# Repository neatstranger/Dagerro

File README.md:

# Dagerro
>The first known attempt at astronomical photography was by Louis Jacques Mandé Daguerre, inventor of the daguerreotype process which bears his name, who attempted in 1839 to photograph the Moon. Tracking errors in guiding the telescope during the long exposure meant the photograph came out as an indistinct fuzzy spot. [Source](https://en.wikipedia.org/wiki/Astrophotography#:~:text=The%20first%20known%20attempt%20at,as%20an%20indistinct%20fuzzy%20spot.)

# Guide Timing
Some notes for myself as well as anyone reading. 
We need to move the steppers about 8 times per second and the Real Time Clock(RTC) doesn't allow for time resolution greater than 1 second. 
The RTC(DS3231) outputs 32,768 pulses per second on the 32K pin. We attach an interrupt to that pin with the following line.

`attachInterrupt(digitalPinToInterrupt(interruptPin), countCycles, CHANGE);`

Note the use of the `CHANGE` for activation. This means that we will capture one interrupt for each rise, and one for each fall.
With our second now divided up into 65,536 segments.

```
1 Degree = 60 ArcMinutes
1 ArcMinute = 60 ArcSeconds
1 Degree = 3600 ArcSeconds
```

How fast does the earth rotate? My previous assumption of ~1ArcSecond/Second~ is wrong. Let's do the math.
```
360° = 24 Hours
15° = 1 Hour or 60 Minutes or 3600 Seconds
1° or 3600 ArcSeconds = 4 Minutes or 240 Seconds
Math = 3600(ArcSeconds-Angle)/240 (Seconds-Time)
15 ArcSeconds(Angle) = 1 Second(Time)

```

The arduino receive exactly 1,658,880 pulses every 25.3125 seconds.
During this period of time, we need to take exactly 1500 steps.

python function to solve the problem.

```
x = 1
maxcount = 1500
xmult = 1105
ymult = 1107

while x <= maxcount:
    y = maxcount - x
    if (xmult*x)+(ymult*y) == 1658880:
        print(x)
        print(y)
        print((xmult*x) + (ymult*y))
    x+=1
```
I used this script, changing the values for xmult and ymult, until I got a result that looks like this:

```
810
690
1658880

```
Which means that if we take a step every 1105 interrupts, 810 times.
Followed by taking a step every 1107 interrupts, 690 times. 
We will have taken 1500 steps in exactly 25.3125 seconds. 

```
1500 Steps * 0.253125 ArcSeconds Per Step = 379.6875 ArcSeconds
379.6875 ArcSeconds / 25.3125 Seconds
15 ArcSeconds / Second
```

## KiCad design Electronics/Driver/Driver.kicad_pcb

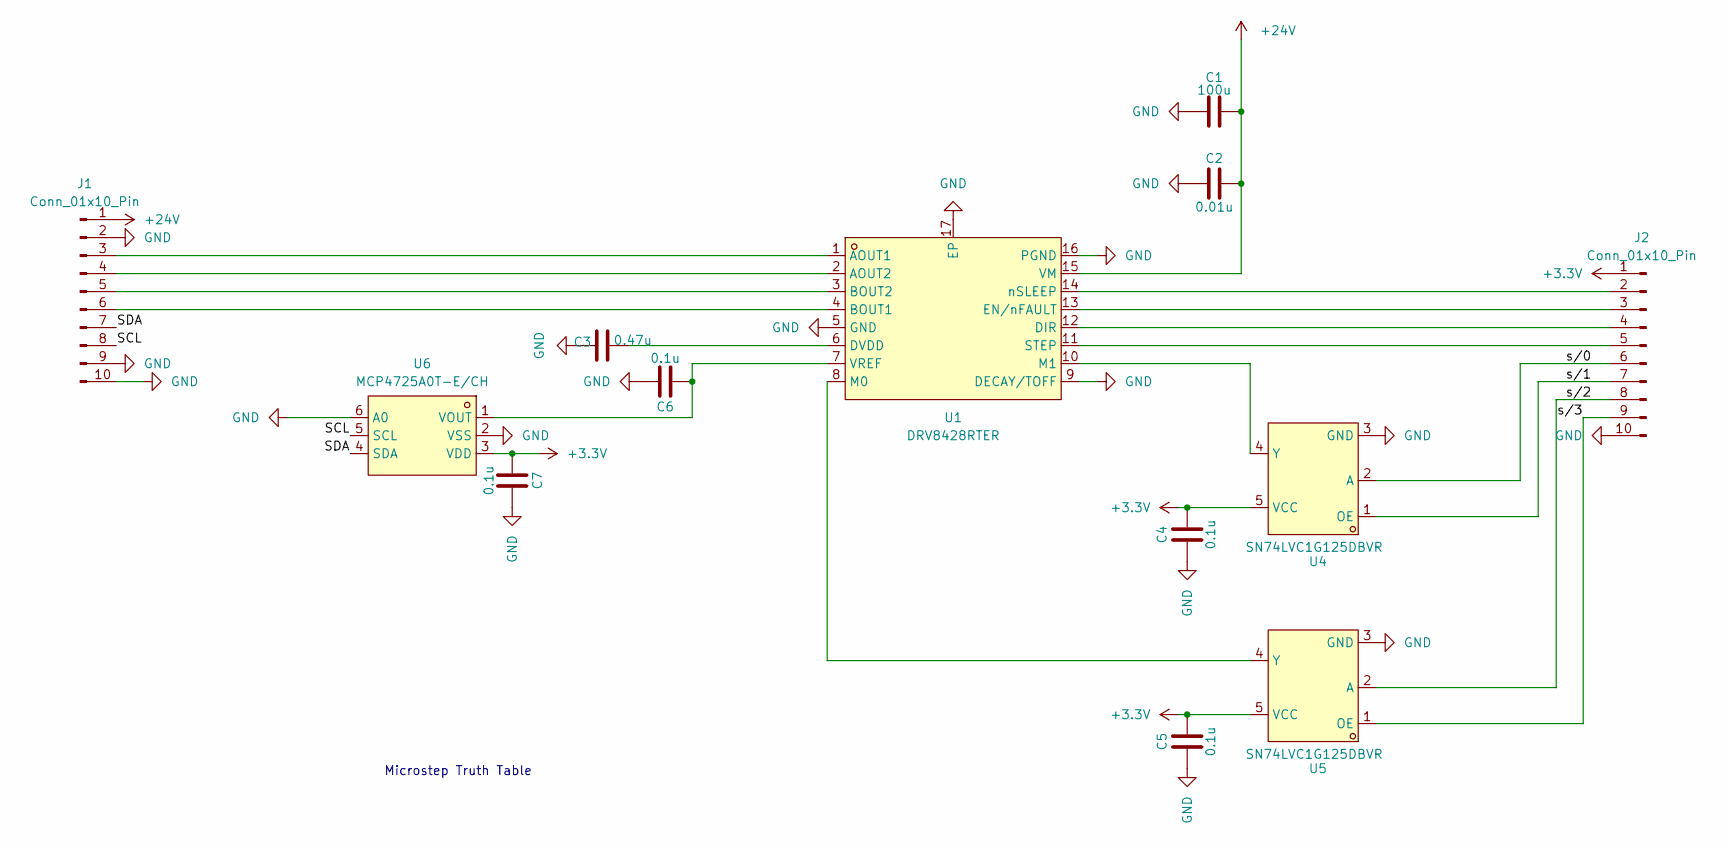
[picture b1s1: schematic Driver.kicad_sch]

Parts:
C1: 100u; C_1206_3216Metric_Pad1.33x1.80mm_HandSolder
C2: 0.01u; C_1206_3216Metric_Pad1.33x1.80mm_HandSolder
C3: 0.47u; C_1206_3216Metric_Pad1.33x1.80mm_HandSolder
C4, C5, C6, C7: 0.1u; C_1206_3216Metric_Pad1.33x1.80mm_HandSolder
J1, J2: Conn_01x10_Pin; PinSocket_1x10_P2.54mm_Vertical
U1: DRV8428RTER; WQFN-16_L3.0-W3.0-P0.50-BL-EP1.7; LCSC Part C2857955
U4, U5: SN74LVC1G125DBVR; SOT-23-5_L3.0-W1.7-P0.95-LS2.8-BL; LCSC Part C23654
U6: MCP4725A0T-E/CH; SOT-23-6_L2.9-W1.6-P0.95-LS2.8-BL; LCSC Part C144198

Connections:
+3.3V: C4.2, C5.2, C7.2, J2.1, U4.5 (VCC), U5.5 (VCC), U6.3 (VDD)
+24V: C1.2, C2.2, J1.1, U1.15 (VM)
/SCL: J1.8, U6.5 (SCL)
/SDA: J1.7, U6.4 (SDA)
GND: C1.1, C2.1, C3.1, C4.1, C5.1, C6.1, C7.1, J1.2, J1.9, J1.10, J2.10, U1.5 (GND), U1.9 (DECAY/TOFF), U1.16 (PGND), U1.17 (EP), U4.3 (GND), U5.3 (GND), U6.2 (VSS), U6.6 (A0)
unnamed: J1.3, U1.1 (AOUT1)
unnamed: J1.4, U1.2 (AOUT2)
unnamed: J1.5, U1.3 (BOUT2)
unnamed: J1.6, U1.4 (BOUT1)
unnamed: J2.2, U1.14 (nSLEEP)
unnamed: J2.3, U1.13 (EN/nFAULT)
unnamed: J2.4, U1.12 (DIR)
unnamed: J2.5, U1.11 (STEP)
unnamed: J2.6, U4.2 (A)
unnamed: J2.7, U4.1 (OE)
unnamed: J2.8, U5.2 (A)
unnamed: J2.9, U5.1 (OE)
unnamed: C3.2, U1.6 (DVDD)
unnamed: U1.8 (M0), U5.4 (Y)
unnamed: U1.10 (M1), U4.4 (Y)
unnamed: C6.2, U1.7 (VREF), U6.1 (VOUT)

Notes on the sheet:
Microstep Truth Table

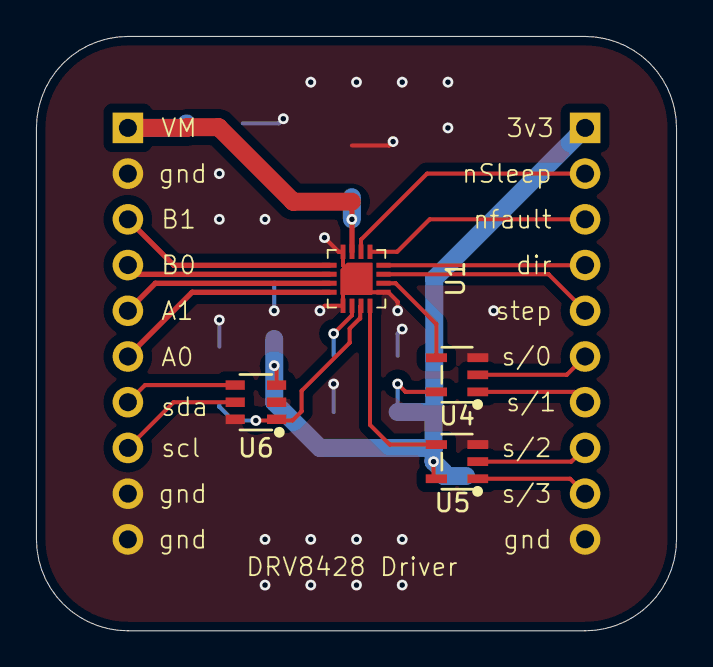
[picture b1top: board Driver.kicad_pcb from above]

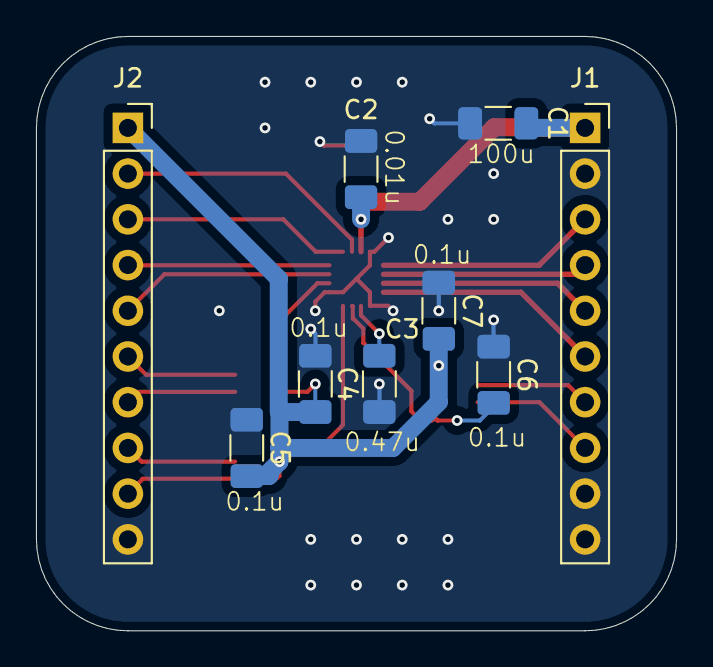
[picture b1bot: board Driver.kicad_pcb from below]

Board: 2 copper layers, 35.6 x 33.0 mm, 13 parts (9 on the bottom side), 21 nets.

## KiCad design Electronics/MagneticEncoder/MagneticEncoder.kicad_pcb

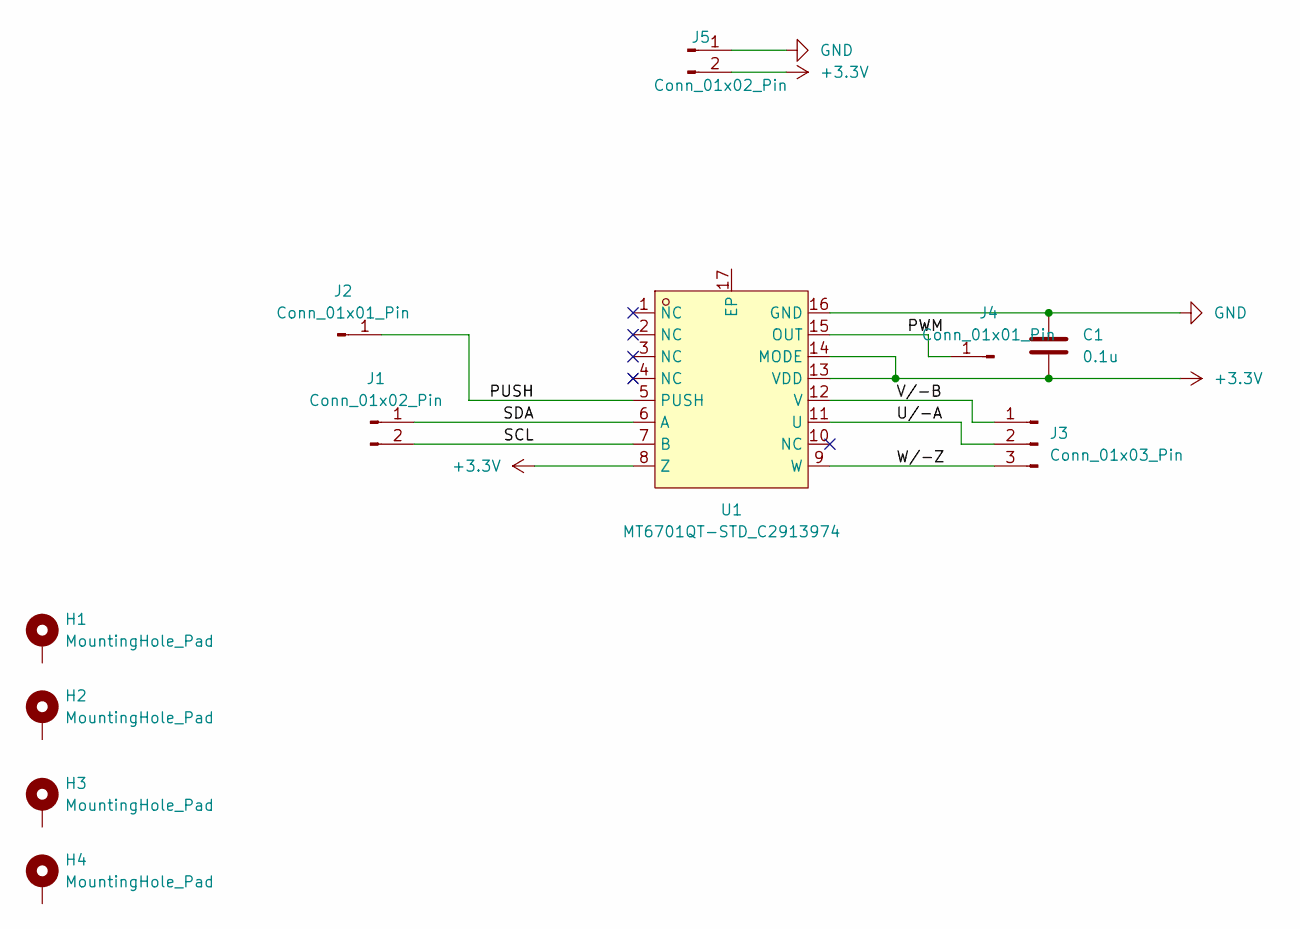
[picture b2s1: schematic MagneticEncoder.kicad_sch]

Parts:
C1: 0.1u; C_1206_3216Metric_Pad1.33x1.80mm_HandSolder
H1, H2, H3, H4: MountingHole_Pad; MountingHole_3.2mm_M3_DIN965_Pad_TopBottom
J1, J5: Conn_01x02_Pin; PinHeader_1x02_P2.54mm_Vertical
J2, J4: Conn_01x01_Pin; PinHeader_1x01_P2.54mm_Vertical
J3: Conn_01x03_Pin; PinHeader_1x03_P2.54mm_Vertical
U1: MT6701QT-STD_C2913974; QFN-16_L3.0-W3.0-P0.50-TL-EP1.7; LCSC Part C2913974

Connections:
+3.3V: C1.2, J5.2, U1.8 (Z), U1.13 (VDD), U1.14 (MODE)
/PUSH: J2.1, U1.5 (PUSH)
/PWM: J4.1, U1.15 (OUT)
/SCL: J1.2, U1.7 (B)
/SDA: J1.1, U1.6 (A)
/U/-A: J3.2, U1.11 (U)
/V/-B: J3.1, U1.12 (V)
/W/-Z: J3.3, U1.9 (W)
GND: C1.1, J5.1, U1.16 (GND)

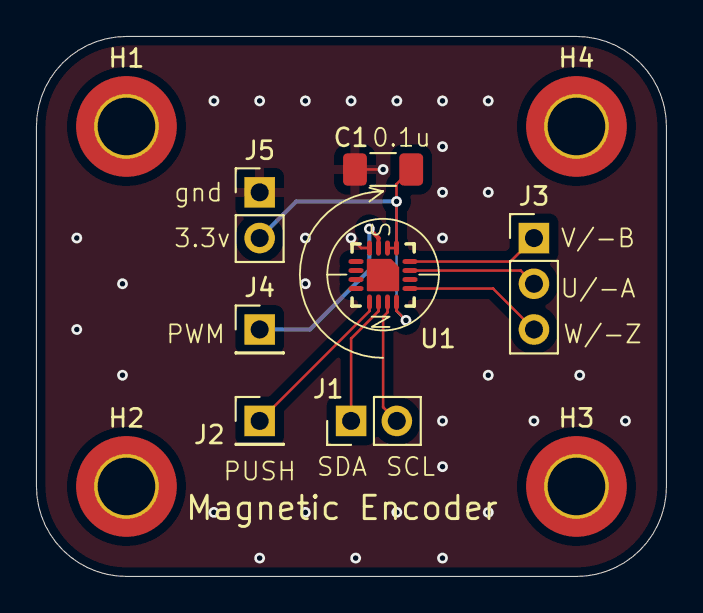
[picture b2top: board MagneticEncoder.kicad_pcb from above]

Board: 2 copper layers, 35.0 x 30.0 mm, 11 parts (0 on the bottom side), 9 nets.

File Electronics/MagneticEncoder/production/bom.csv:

Designator,Footprint,Quantity,Value,LCSC Part #
C1,1206,1,0.1u,
"J1, J5",PinHeader_1x02_P2.54mm_Vertical,2,Conn_01x02_Pin,
"J2, J4",PinHeader_1x01_P2.54mm_Vertical,2,Conn_01x01_Pin,
J3,PinHeader_1x03_P2.54mm_Vertical,1,Conn_01x03_Pin,
U1,QFN-16_L3.0-W3.0-P0.50-TL-EP1.7,1,MT6701QT-STD_C2913974,C2913974

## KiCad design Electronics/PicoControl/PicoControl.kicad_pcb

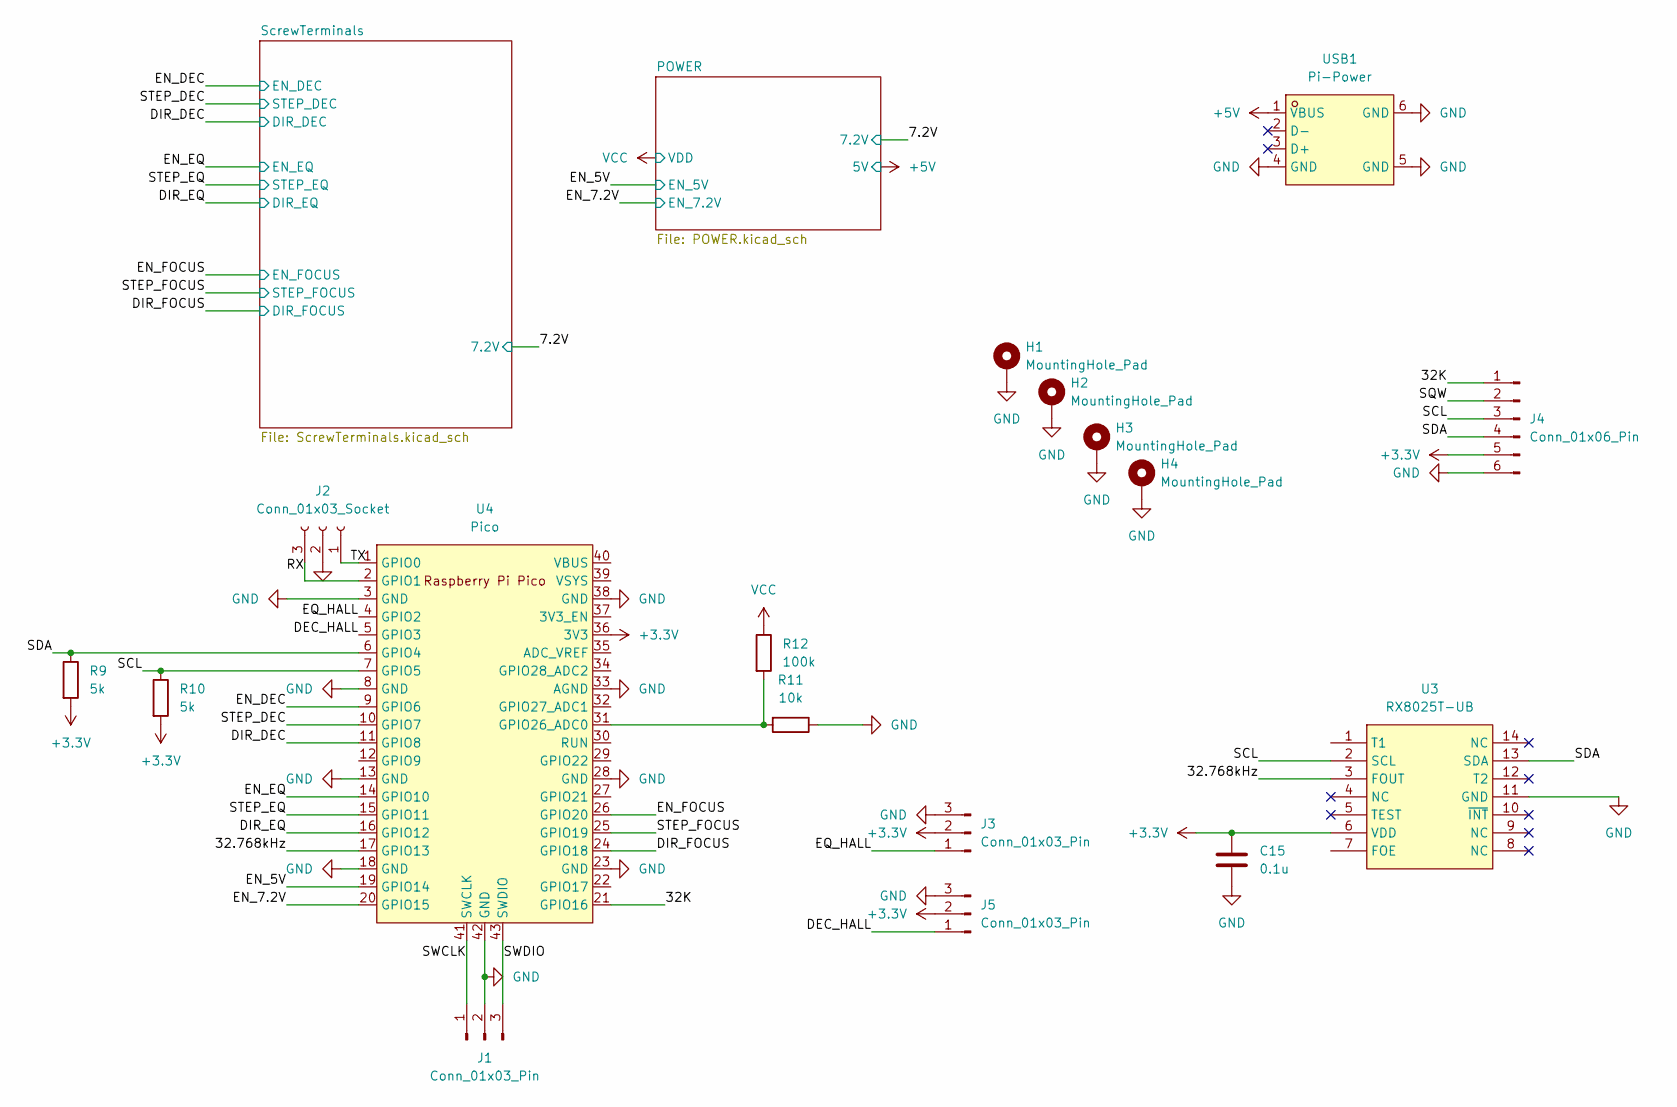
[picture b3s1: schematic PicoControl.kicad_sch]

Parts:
C15: 0.1u; C_1206_3216Metric_Pad1.33x1.80mm_HandSolder
H1, H2, H3, H4: MountingHole_Pad; MountingHole_5.3mm_M5_DIN965_Pad
J1: Conn_01x03_Pin; PinHeader_1x03_P2.54mm_Vertical
J2: Conn_01x03_Socket; PinHeader_1x03_P2.54mm_Vertical
J3, J5: Conn_01x03_Pin; PinHeader_1x03_P2.54mm_Horizontal
J4: Conn_01x06_Pin; PinHeader_1x06_P2.54mm_Vertical
R9, R10: 5k; R_1206_3216Metric_Pad1.30x1.75mm_HandSolder
R11: 10k; R_1206_3216Metric_Pad1.30x1.75mm_HandSolder
R12: 100k; R_1206_3216Metric_Pad1.30x1.75mm_HandSolder
U3: RX8025T-UB; SOIC-14_L10.1-W5.0-P1.27-LS7.4-BL; LCSC Part C17353
U4: Pico; RPi_Pico_SMD_TH
USB1: Pi-Power; USB-A-TH_USB-231-ARY; LCSC Part C720525

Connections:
+3.3V: C15.2, J3.2, J4.5, J5.2, R9.2, R10.2, U3.6 (VDD), U4.36 (3V3)
+5V: USB1.1 (VBUS); also elsewhere on the board
/32.768kHz: U3.3 (FOUT), U4.17 (GPIO13)
/32K: J4.1, U4.21 (GPIO16)
/DEC_HALL: J5.1, U4.5 (GPIO3)
/DIR_DEC: U4.11 (GPIO8); also elsewhere on the board
/DIR_EQ: U4.16 (GPIO12); also elsewhere on the board
/DIR_FOCUS: U4.24 (GPIO18); also elsewhere on the board
/EN_5V: U4.19 (GPIO14); also elsewhere on the board
/EN_7.2V: U4.20 (GPIO15); also elsewhere on the board
/EN_DEC: U4.9 (GPIO6); also elsewhere on the board
/EN_EQ: U4.14 (GPIO10); also elsewhere on the board
/EN_FOCUS: U4.26 (GPIO20); also elsewhere on the board
/EQ_HALL: J3.1, U4.4 (GPIO2)
/RX: J2.3, U4.2 (GPIO1)
/SCL: J4.3, R10.1, U3.2 (SCL), U4.7 (GPIO5)
/SDA: J4.4, R9.1, U3.13 (SDA), U4.6 (GPIO4)
/SQW: J4.2
/STEP_DEC: U4.10 (GPIO7); also elsewhere on the board
/STEP_EQ: U4.15 (GPIO11); also elsewhere on the board
/STEP_FOCUS: U4.25 (GPIO19); also elsewhere on the board
/SWCLK: J1.1, U4.41 (SWCLK)
/SWDIO: J1.3, U4.43 (SWDIO)
/TX: J2.1, U4.1 (GPIO0)
GND: C15.1, H1.1, H2.1, H3.1, H4.1, J1.2, J2.2, J3.3, J4.6, J5.3, R11.1, U3.11 (GND), U4.3 (GND), U4.8 (GND), U4.13 (GND), U4.18 (GND), U4.23 (GND), U4.28 (GND), U4.33 (AGND), U4.38 (GND), U4.42 (GND), USB1.4 (GND), USB1.5 (GND), USB1.6 (GND); also elsewhere on the board
unnamed: R11.2, R12.2, U4.31 (GPIO26_ADC0)
VCC: R12.1; also elsewhere on the board

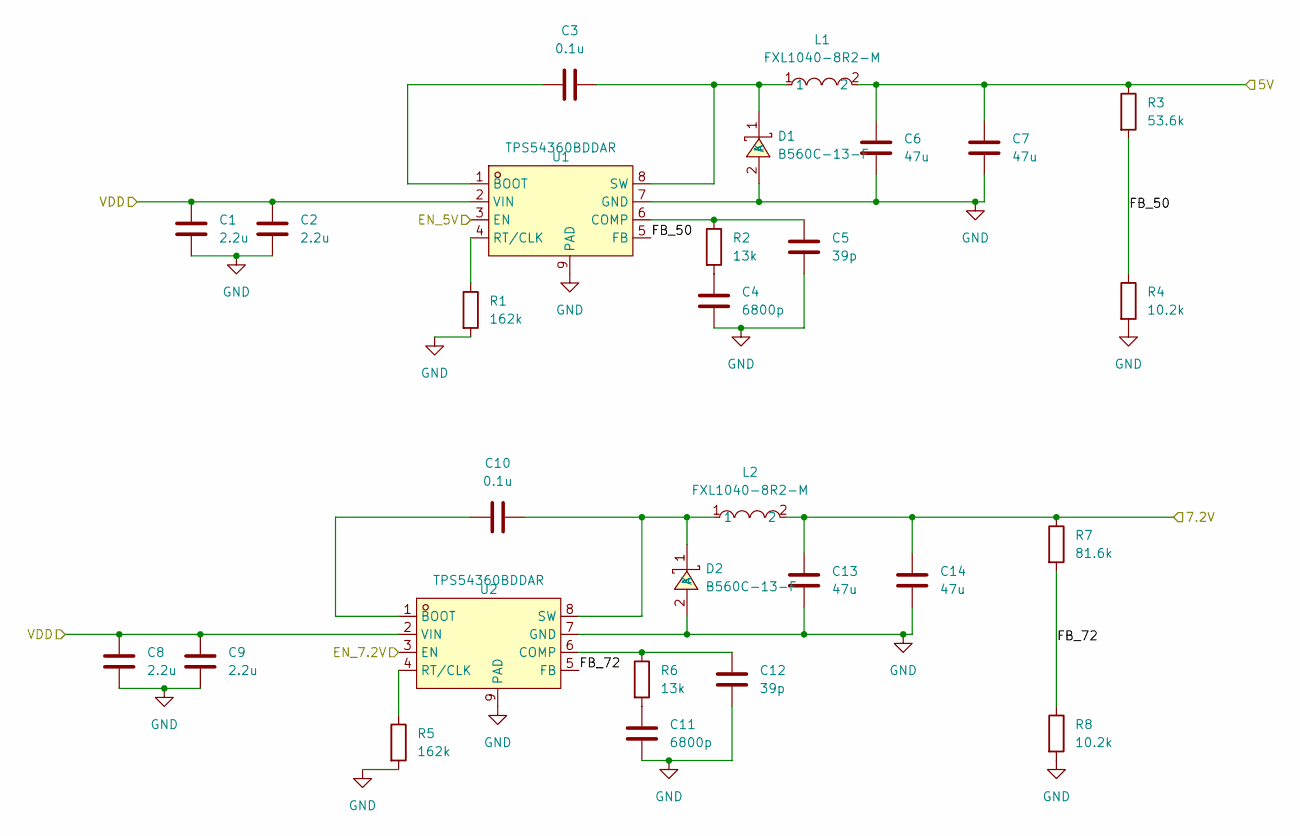
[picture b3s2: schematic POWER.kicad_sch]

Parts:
C1, C2, C8, C9: 2.2u; C_1206_3216Metric; LCSC Part C170101
C3, C10: 0.1u; C_1206_3216Metric_Pad1.33x1.80mm_HandSolder; LCSC Part C56392
C4, C11: 6800p; C_1206_3216Metric_Pad1.33x1.80mm_HandSolder; LCSC Part C2760541
C5, C12: 39p; C_1206_3216Metric_Pad1.33x1.80mm_HandSolder; LCSC Part C5186878
C6, C7, C13, C14: 47u; C_1206_3216Metric; LCSC Part C94034
D1, D2: B560C-13-F; SMC_L7.1-W6.2-LS8.1-RD; LCSC Part C85100
L1, L2: FXL1040-8R2-M; IND-SMD_L11.5-W10.0_FXL1040; LCSC Part C167232
R1, R5: 162k; R_1206_3216Metric_Pad1.30x1.75mm_HandSolder; LCSC Part C22815
R2, R6: 13k; R_1206_3216Metric_Pad1.30x1.75mm_HandSolder; LCSC Part C445658
R3: 53.6k; R_1206_3216Metric_Pad1.30x1.75mm_HandSolder; LCSC Part C21398
R4, R8: 10.2k; R_1206_3216Metric_Pad1.30x1.75mm_HandSolder; LCSC Part C217771
R7: 81.6k; R_1206_3216Metric_Pad1.30x1.75mm_HandSolder; LCSC Part C21398
U1, U2: TPS54360BDDAR; SOIC-8_L5.0-W4.0-P1.27-LS6.0-BL-EP2.0; LCSC Part C524806

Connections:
+5V: C6.1, C7.1, L1.2, R3.1; also elsewhere on the board
/7.2V: C13.1, C14.1, L2.2, R7.1; also elsewhere on the board
/EN_5V: U1.3 (EN); also elsewhere on the board
/EN_7.2V: U2.3 (EN); also elsewhere on the board
/POWER/FB_50: R3.2, R4.1, U1.5 (FB)
/POWER/FB_72: R7.2, R8.1, U2.5 (FB)
GND: C1.2, C2.2, C4.2, C5.2, C6.2, C7.2, C8.2, C9.2, C11.2, C12.2, C13.2, C14.2, D1.2 (A), D2.2 (A), R1.2, R4.2, R5.2, R8.2, U1.7 (GND), U1.9 (PAD), U2.7 (GND), U2.9 (PAD); also elsewhere on the board
unnamed: C4.1, R2.2
unnamed: C11.1, R6.2
unnamed: C3.2, D1.1 (K), L1.1, U1.8 (SW)
unnamed: C10.2, D2.1 (K), L2.1, U2.8 (SW)
unnamed: C3.1, U1.1 (BOOT)
unnamed: C5.1, R2.1, U1.6 (COMP)
unnamed: R1.1, U1.4 (RT/CLK)
unnamed: C10.1, U2.1 (BOOT)
unnamed: C12.1, R6.1, U2.6 (COMP)
unnamed: R5.1, U2.4 (RT/CLK)
VCC: C1.1, C2.1, C8.1, C9.1, U1.2 (VIN), U2.2 (VIN); also elsewhere on the board

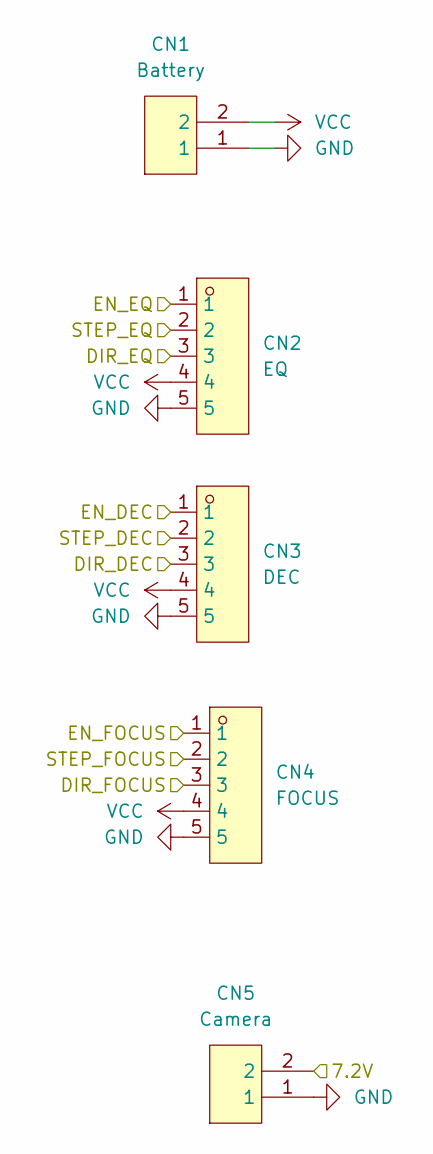
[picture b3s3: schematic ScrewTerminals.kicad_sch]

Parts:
CN1: Battery; CONN-TH_2P-P5.00_WJ500V-5.08-2P; LCSC Part C8465
CN2: EQ; CONN-TH_5P-P5.08_DIBO_DB128V-5.08-5P-GN-S; LCSC Part C2927513
CN3: DEC; CONN-TH_5P-P5.08_DIBO_DB128V-5.08-5P-GN-S; LCSC Part C2927513
CN4: FOCUS; CONN-TH_5P-P5.08_DIBO_DB128V-5.08-5P-GN-S; LCSC Part C2927513
CN5: Camera; CONN-TH_2P-P5.00_WJ500V-5.08-2P; LCSC Part C8465

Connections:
/7.2V: CN5.2; also elsewhere on the board
/DIR_DEC: CN3.3; also elsewhere on the board
/DIR_EQ: CN2.3; also elsewhere on the board
/DIR_FOCUS: CN4.3; also elsewhere on the board
/EN_DEC: CN3.1; also elsewhere on the board
/EN_EQ: CN2.1; also elsewhere on the board
/EN_FOCUS: CN4.1; also elsewhere on the board
/STEP_DEC: CN3.2; also elsewhere on the board
/STEP_EQ: CN2.2; also elsewhere on the board
/STEP_FOCUS: CN4.2; also elsewhere on the board
GND: CN1.1, CN2.5, CN3.5, CN4.5, CN5.1; also elsewhere on the board
VCC: CN1.2, CN2.4, CN3.4, CN4.4; also elsewhere on the board

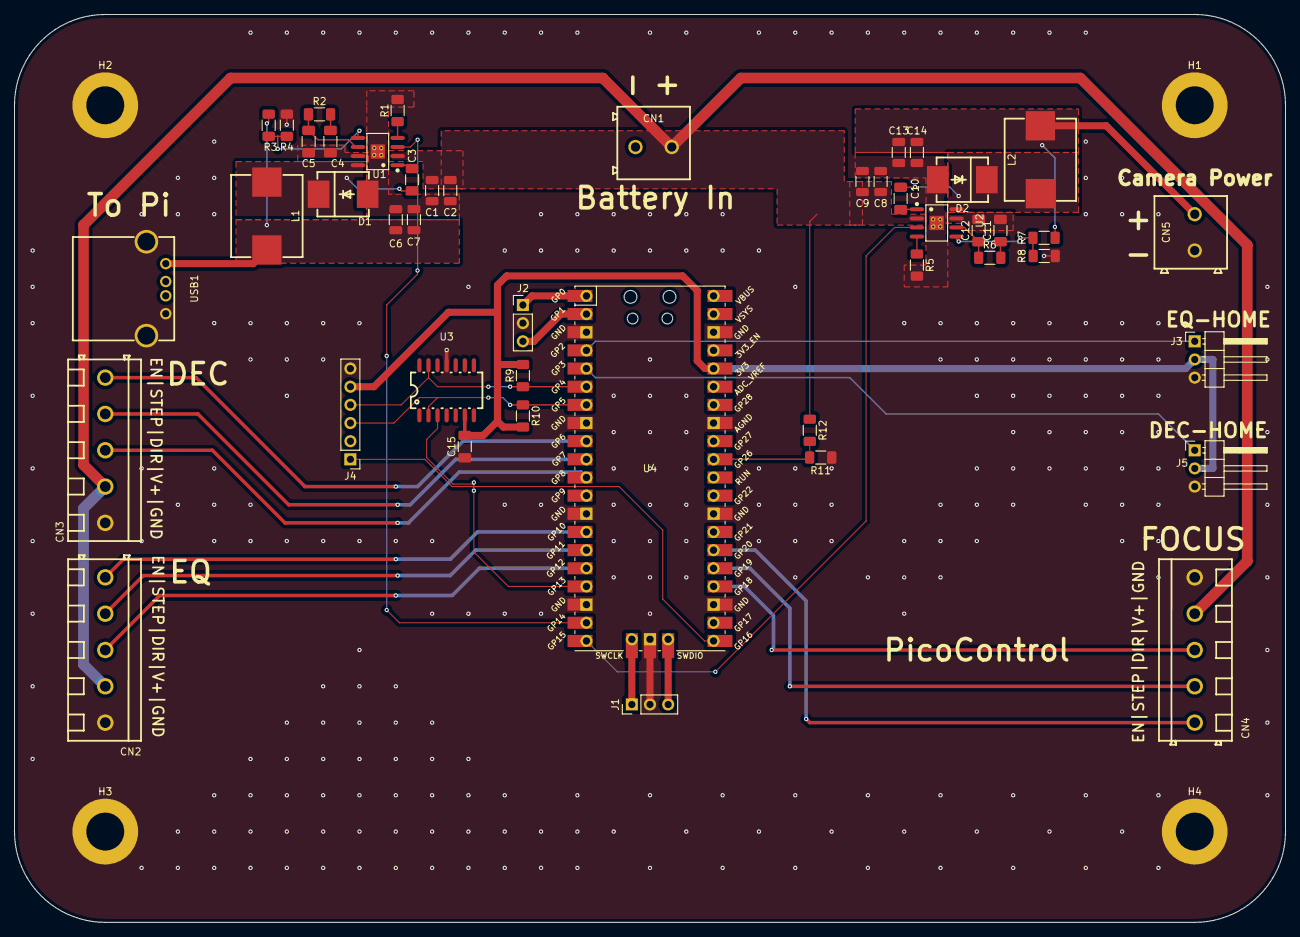
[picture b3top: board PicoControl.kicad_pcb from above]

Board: 2 copper layers, 177.8 x 127.0 mm, 50 parts (0 on the bottom side), 39 nets.

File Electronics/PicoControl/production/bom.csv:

Designator,Footprint,Quantity,Value,LCSC Part #
"C1, C2, C8, C9",1206,4,2.2u,C170101
"C10, C3",1206,2,0.1u,C56392
"C11, C4",1206,2,6800p,C2760541
"C12, C5",1206,2,39p,C5186878
"C13, C14, C6, C7",1206,4,47u,C94034
C15,1206,1,0.1u,
CN1,CONN-TH_2P-P5.00_WJ500V-5.08-2P,1,Battery,C8465
CN2,CONN-TH_5P-P5.08_DIBO_DB128V-5.08-5P-GN-S,1,EQ,C2927513
CN3,CONN-TH_5P-P5.08_DIBO_DB128V-5.08-5P-GN-S,1,DEC,C2927513
CN4,CONN-TH_5P-P5.08_DIBO_DB128V-5.08-5P-GN-S,1,FOCUS,C2927513
CN5,CONN-TH_2P-P5.00_WJ500V-5.08-2P,1,Camera,C8465
"D1, D2",SMC_L7.1-W6.2-LS8.1-RD,2,B560C-13-F,C85100
J1,PinHeader_1x03_P2.54mm_Vertical,1,Conn_01x03_Pin,
J2,PinHeader_1x03_P2.54mm_Vertical,1,Conn_01x03_Socket,
J4,PinHeader_1x06_P2.54mm_Vertical,1,Conn_01x06_Pin,
"L1, L2",IND-SMD_L11.5-W10.0_FXL1040,2,FXL1040-8R2-M,C167232
"R1, R5",1206,2,162k,C22815
"R10, R9",1206,2,5k,
R11,1206,1,10k,
R12,1206,1,100k,
"R2, R6",1206,2,13k,C445658
R3,1206,1,53.6k,C21398
"R4, R8",1206,2,10.2k,C217771
R7,1206,1,81.6k,C21398
"U1, U2",SOIC-8_L5.0-W4.0-P1.27-LS6.0-BL-EP2.0,2,TPS54360BDDAR,C524806
U3,SOIC-14_L10.1-W5.0-P1.27-LS7.4-BL,1,RX8025T-UB,C17353
U4,RPi_Pico_SMD_TH,1,Pico,
USB1,USB-A-TH_USB-231-ARY,1,Pi-Power,C720525

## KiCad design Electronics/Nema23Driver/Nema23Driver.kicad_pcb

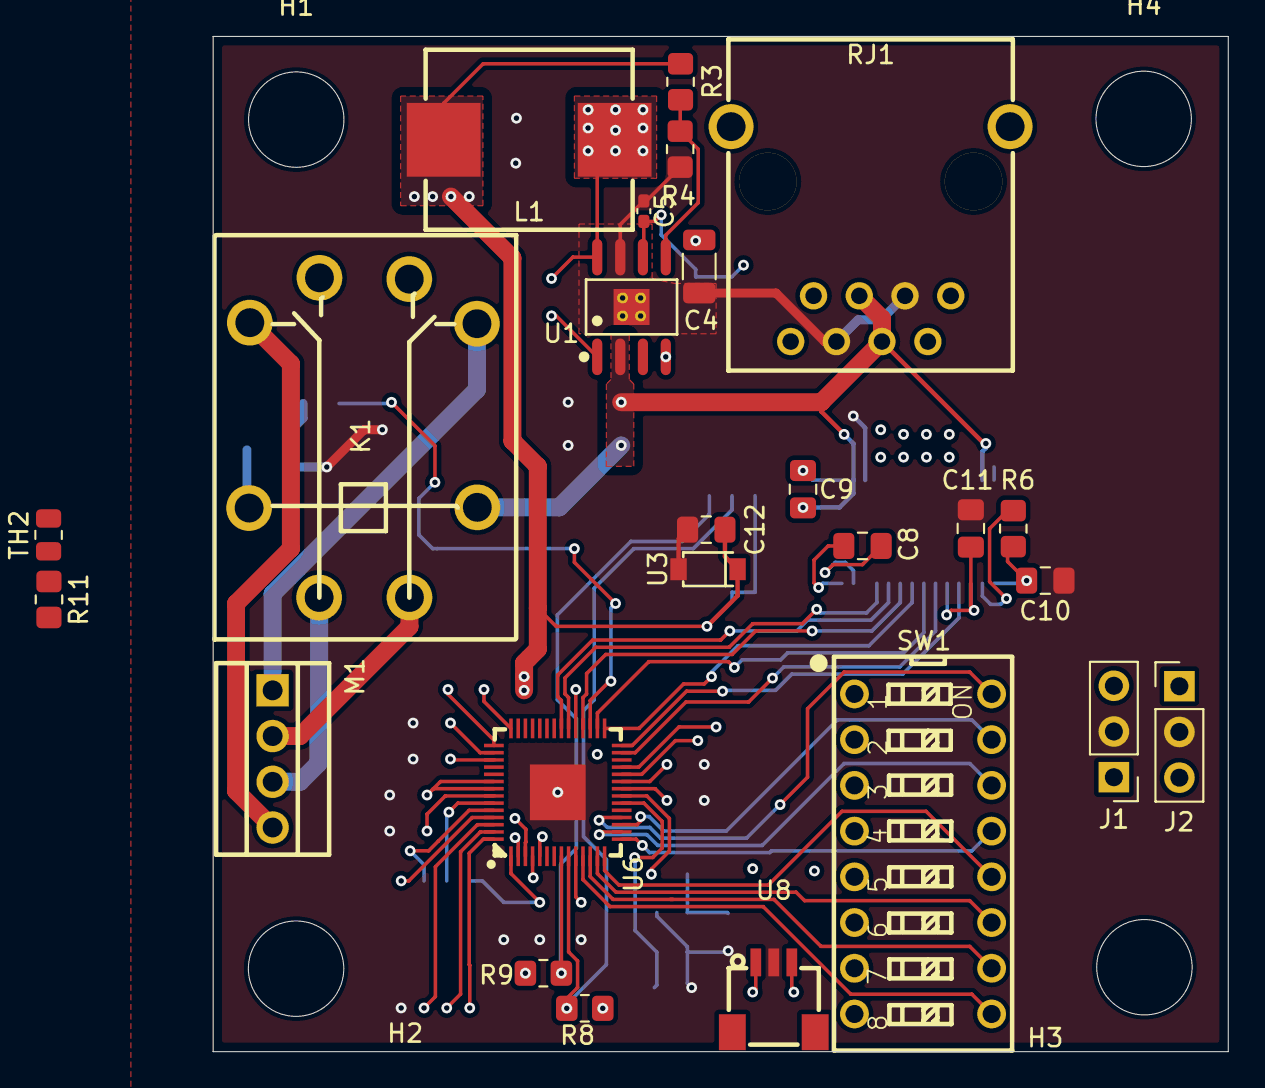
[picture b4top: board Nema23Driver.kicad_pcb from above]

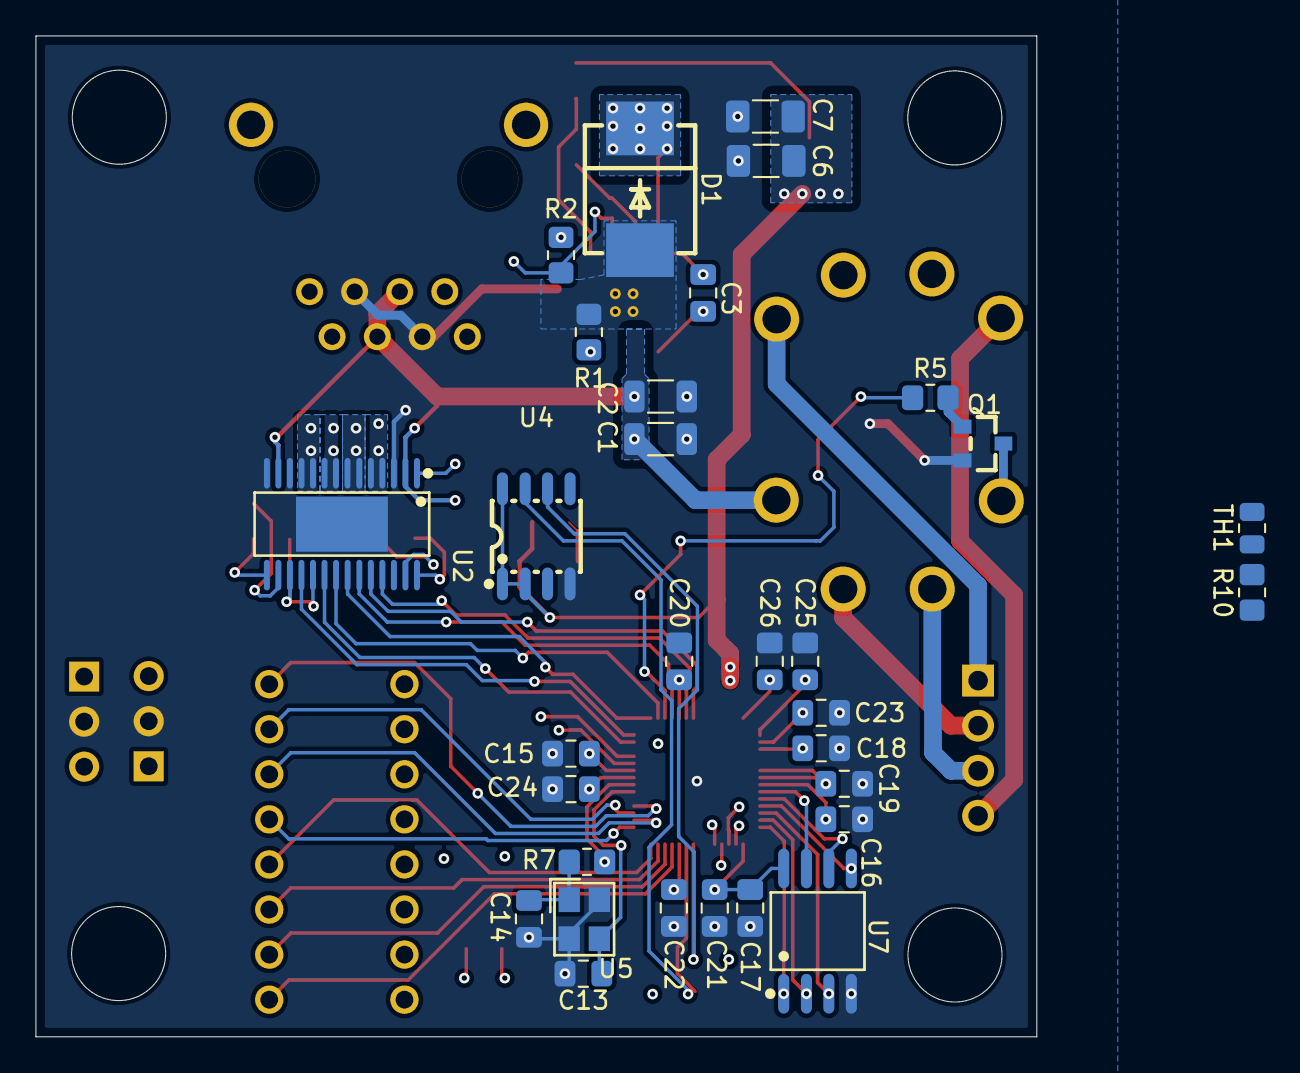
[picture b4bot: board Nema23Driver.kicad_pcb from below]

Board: 4 copper layers, 56.4 x 56.4 mm, 60 parts (31 on the bottom side), 58 nets.

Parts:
C1, C2: 2.2u; C_1206_3216Metric
C3, C11, C12, C15, C16, C17, C20, C21, C22, C23, C24, C25, C26: 0.1u; C_0805_2012Metric_Pad1.18x1.45mm_HandSolder
C4: 6800p; C_1206_3216Metric
C5: 39p; C_0402_1005Metric_Pad0.74x0.62mm_HandSolder
C6, C7: 47u; C_1206_3216Metric_Pad1.33x1.80mm_HandSolder
C8: 0.022u; C_0805_2012Metric_Pad1.18x1.45mm_HandSolder
C9: 0.22u; C_0805_2012Metric_Pad1.18x1.45mm_HandSolder
C10: 0.47u; C_0805_2012Metric_Pad1.18x1.45mm_HandSolder
C13, C14: 15p; C_0805_2012Metric_Pad1.18x1.45mm_HandSolder
C18, C19: 1u; C_0805_2012Metric_Pad1.18x1.45mm_HandSolder
D1: B560C-13-F; SMC_L7.1-W6.2-LS8.1-RD
H1, H2, H3, H4: MountingHole_Pad; MountingHole_5.3mm_M5
J1, J2: Conn_01x03_Socket; PinHeader_1x03_P2.54mm_Vertical
K1: SRE-24VDC-SL-2C; RELAY-TH_SRE-12VDC-SL-2C
L1: FXL1040-8R2-M; IND-SMD_L11.5-W10.0_FXL1040
M1: Stepper_Motor_bipolar; CONN-TH_DB125-2.54-4P-GN
Q1: AO3400_C2938367; SOT-23_L2.9-W1.3-P1.90-LS2.4-BR
R1: 162k; R_0805_2012Metric_Pad1.20x1.40mm_HandSolder
R2: 13k; R_0805_2012Metric_Pad1.20x1.40mm_HandSolder
R3: 31.6k; R_0805_2012Metric_Pad1.20x1.40mm_HandSolder
R4: 10.2k; R_0805_2012Metric_Pad1.20x1.40mm_HandSolder
R5, R7: 1k; R_0805_2012Metric_Pad1.20x1.40mm_HandSolder
R6: 10k; R_0805_2012Metric_Pad1.20x1.40mm_HandSolder
R8, R9, R10, R11: 5k; R_0805_2012Metric_Pad1.20x1.40mm_HandSolder
RJ1: R-RJ45R10P-B000; RJ45-TH_R-RJ45R10P-B000
SW1: DS-08BLP; SW-TH_16P-L21.9-W9.9-P2.54-LS7.6
TH1, TH2: 10K; R_0805_2012Metric
U1: TPS54360BDDAR; SOIC-8_L5.0-W4.0-P1.27-LS6.0-BL-EP2.0
U2: DRV8434SPWPR; HTSSOP-28_L9.7-W4.4-P0.65-LS6.4-BL-EP-5
U3: PTVS6V0S1UR_C18723426; SOD-123_L2.7-W1.6-LS3.7-RD
U4: MT6701CT-STD-R; SOP-8_L4.9-W3.9-P1.27-LS6.0-BL
U5: ABM8-272-T3_C20625731; CRYSTAL-SMD_4P-L3.2-W2.5-BL
U6: RP2040; LQFN-56_L7.0-W7.0-P0.4-EP
U7: W25Q128JVSIQTR; SOIC-8_L5.3-W5.3-P1.27-LS8.0-BL
U8: SM03B-SRSS-TB(LF)(SN)(P); CONN-SMD_SM03B-SRSS-TB-LF-SN-P

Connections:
+1V1: C15.2, C16.2, C18.2, U6.23 (DVDD), U6.45 (VREG_VOUT), U6.50 (DVDD)
+3.3V: C6.1, C7.1, C11.2, C12.2, C17.2, C19.2, C20.2, C21.2, C22.2, C23.2, C24.2, C25.2, C26.2, L1.2, R3.1, R8.2, R9.1, SW1.1 (PIN1), SW1.2 (PIN2), SW1.3 (PIN3), SW1.4 (PIN4), SW1.5 (PIN5), SW1.6 (PIN6), SW1.7 (PIN7), SW1.8 (PIN8), TH1.2, TH2.2, U2.17 (VREF), U2.19 (VSDO), U3.1 (K), U4.1 (VDD), U4.2 (MODE), U4.8 (Z), U6.1 (IOVDD), U6.10 (IOVDD), U6.22 (IOVDD), U6.33 (IOVDD), U6.42 (IOVDD), U6.43 (ADC_AVDD), U6.44 (VREG_IN), U6.48 (USB_VDD), U6.49 (IOVDD), U7.8 (VCC)
/DIR: U2.24 (DIR), U6.35 (GPIO23)
/EN: U2.25 (ENBLE), U6.34 (GPIO22)
/EN_MOT: R5.1, U6.31 (GPIO20)
/Magnetic Sensor/SCL: R8.1, U4.7 (B), U6.9 (GPIO7)
/Magnetic Sensor/SDA: R9.2, U4.6 (A), U6.8 (GPIO6)
/Motor/A0: K1.6, M1.2 (-)
/Motor/A0.Enabled: K1.8, U2.4 (AOUT1), U2.5 (AOUT1)
/Motor/A1: K1.7, M1.1, U2.6 (AOUT2), U2.7 (AOUT2)
/Motor/B0: K1.3, M1.3
/Motor/B0.Enabled: K1.5, U2.10 (BOUT1), U2.11 (BOUT1)
/Motor/B1: K1.4, M1.4, U2.8 (BOUT2), U2.9 (BOUT2)
/Motor/CS: U2.18 (NSCS), U6.28 (GPIO17)
/Motor/SCLK: U2.22 (SCLK), U6.29 (GPIO18)
/Motor/SDI: U2.21 (SDI), U6.30 (GPIO19)
/Motor/SDO: U2.20 (SDO), U6.27 (GPIO16)
/Power/Dir: RJ1.8, U6.4 (GPIO2)
/Power/FB: R3.2, R4.1, U1.5 (FB)
/Power/Step: RJ1.1, U6.5 (GPIO3)
/RP2040/ADC2: R11.1, TH2.1, U6.40 (GPIO28_ADC2)
/RP2040/ADC3: R10.1, TH1.1, U6.41 (GPIO29_ADC3)
/RP2040/CLK: U6.52 (QSPI_SCLK), U7.6 (CLK)
/RP2040/D0: U6.53 (QSPI_SD0), U7.5 (DI)
/RP2040/D1: U6.55 (QSPI_SD1), U7.2 (DO)
/RP2040/D2: U6.54 (QSPI_SD2), U7.3 (IO2)
/RP2040/D3: U6.51 (QSPI_SD3), U7.7 (IO3)
/RP2040/SS: U6.56 (QSPI_SS), U7.1 (~CS)
/RP2040/UART0_RX: J1.3, U6.3 (GPIO1)
/RP2040/UART0_TX: J1.1, U6.2 (GPIO0)
/STEP: U2.23 (STEP), U6.32 (GPIO21)
/SWCLK: J2.3, U6.24 (SWCLK), U8.1
/SWDIO: J2.1, U6.25 (SWD), U8.3
GND: C1.2, C2.2, C4.2, C5.2, C6.2, C7.2, C10.1, C11.1, C12.1, C13.2, C14.1, C15.1, C16.1, C17.1, C18.1, C19.1, C20.1, C21.1, C22.1, C23.1, C24.1, C25.1, C26.1, D1.2 (A), J1.2, J2.2, Q1.2 (S), R1.2, R4.2, R10.2, R11.2, RJ1.3, RJ1.6, U1.7 (GND), U1.9 (PAD), U2.3 (PGND), U2.12 (PGND), U2.14 (GND), U2.29 (EP), U3.2 (A), U4.4 (GND), U5.2 (GND), U5.4 (GND), U6.57 (GND), U7.4 (GND), U8.2
unnamed: C4.1, R2.2
unnamed: C14.2, R7.1, U5.1
unnamed: C3.2, D1.1 (K), L1.1, U1.8 (SW)
unnamed: K1.1, Q1.3 (D)
unnamed: Q1.1 (G), R5.2
unnamed: SW1.9 (PIN9), U6.11 (GPIO8)
unnamed: SW1.10 (PIN10), U6.12 (GPIO9)
unnamed: SW1.11 (PIN11), U6.13 (GPIO10)
unnamed: SW1.12 (PIN12), U6.14 (GPIO11)
unnamed: SW1.13 (PIN13), U6.15 (GPIO12)
unnamed: SW1.14 (PIN14), U6.16 (GPIO13)
unnamed: C3.1, U1.1 (BOOT)
unnamed: C5.1, R2.1, U1.6 (COMP)
unnamed: R1.1, U1.4 (RT/CLK)
unnamed: C8.2, U2.28 (CPH)
unnamed: C8.1, U2.27 (CPL)
unnamed: C10.2, R6.2, U2.15 (DVDD)
unnamed: C9.2, U2.1 (VCP)
unnamed: R6.1, U2.16 (nFAULT)
unnamed: SW1.15, U6.17 (GPIO14)
unnamed: SW1.16, U6.18 (GPIO15)
unnamed: C13.1, U5.3, U6.20 (XIN)
unnamed: R7.2, U6.21 (XOUT)
VDD: C1.1, C2.1, C9.1, K1.2, RJ1.4, RJ1.5, U1.2 (VIN), U2.2 (VM), U2.13 (VM)
